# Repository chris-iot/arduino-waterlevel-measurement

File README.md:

# arduino-waterlevel-measurement
An Arduino based water level measurement that can e.g. be used to detect the fill level of your cistern

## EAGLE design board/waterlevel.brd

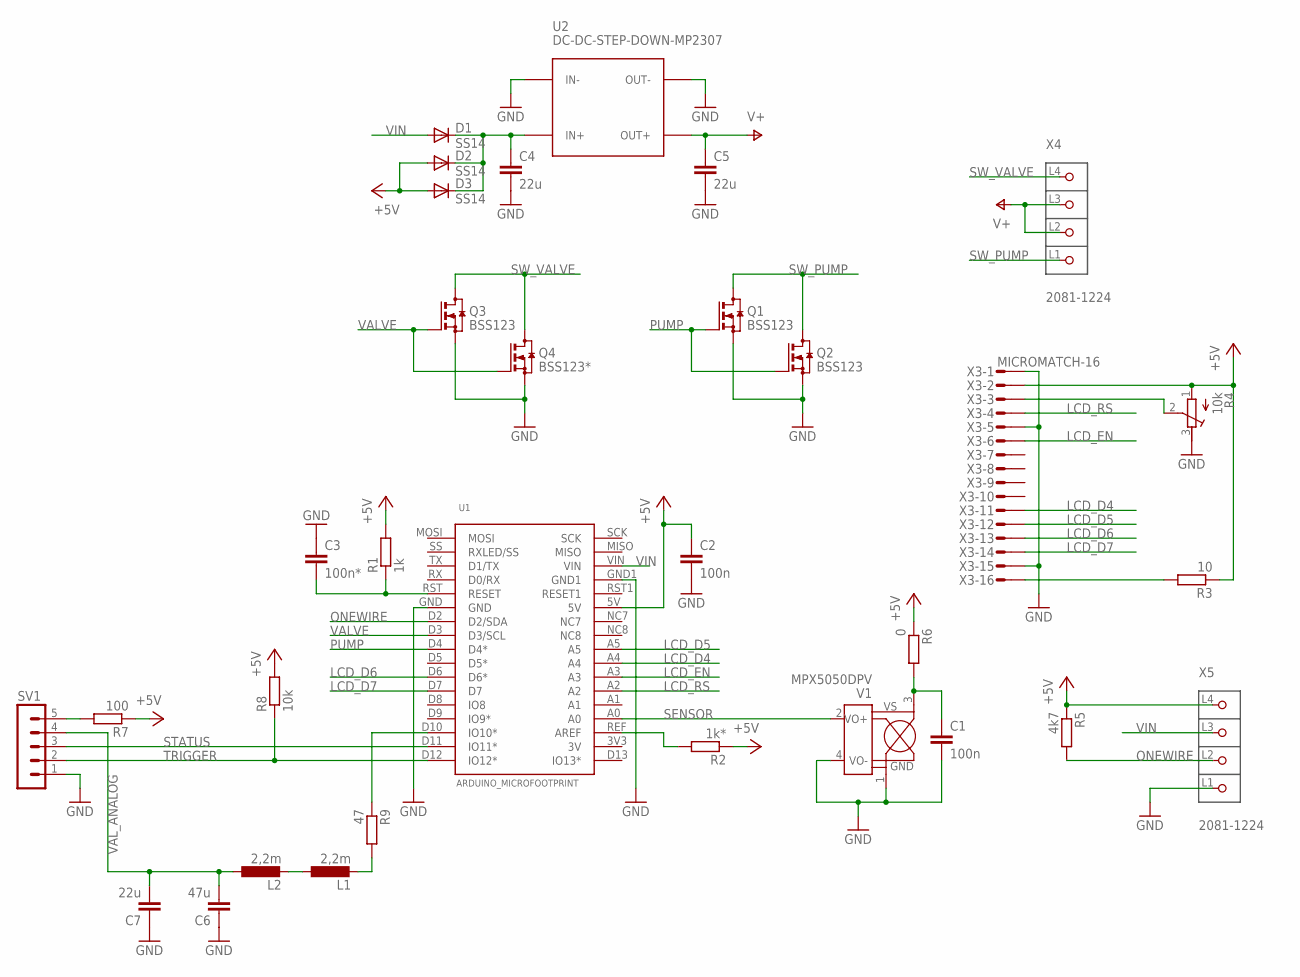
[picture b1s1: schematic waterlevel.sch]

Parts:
C1, C2: 100n; C0603
C3: 100n*; C0603
C4, C5: 22u; C1210K
C6: 47u; C1206K
C7: 22u; C1206K
D1, D2, D3: SS14; DO214AC
L1, L2: 2,2m; L1812
Q1, Q2, Q3: BSS123; SOT23
Q4: BSS123*; SOT23
R1: 1k; R0603
R2: 1k*; R0603
R3: 10; R0603
R4: 10k; RTRIM64Z
R5: 4k7; R0603
R6: 0; R0603
R7: 100; R0603
R8: 10k; R0603
R9: 47; R0603
SV1: MA05-1
U1: ARDUINO_MICROFOOTPRINT; ARDUINO-MICRO
U2: DC-DC-STEP-DOWN-MP2307
V1: MPX5050DPV; MPX2050DPV
X3: MICROMATCH-16
X4, X5: 2081-1224; P-2081-1224

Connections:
+5V: C2.1, D2.A, D3.A, R1.2, R2.1, R3.1, R4.1 (A), R5.1, R6.1, R7.1, R8.2, U1.5V, X3.2, X5.L4 (P4)
GND: C1.2, C2.2, C3.1, C4.2, C5.2, C6.1, C7.1, Q1.2 (S), Q2.2 (S), Q3.2 (S), Q4.2 (S), R4.3 (E), SV1.1, U1.GND, U1.GND1, U2.IN-, U2.OUT-, V1.1 (GND), V1.4 (VO-), X3.1, X3.5, X3.15, X5.L1 (P1)
LCD_D4: U1.A4, X3.11
LCD_D5: U1.A5, X3.12
LCD_D6: U1.D6 (D6*), X3.13
LCD_D7: U1.D7, X3.14
LCD_EN: U1.A3, X3.6
LCD_RS: U1.A2, X3.4
unnamed: C4.1, D1.C, D2.C, D3.C, U2.IN+
unnamed: C3.2, R1.1, U1.RST (RESET)
unnamed: R2.2, U1.REF (AREF)
unnamed: R4.2 (S), X3.3
unnamed: C1.1, R6.2, V1.3 (VS)
unnamed: R7.2, SV1.5
unnamed: R9.1, U1.D10 (IO10*)
unnamed: R3.2, X3.16
unnamed: L1.2, R9.2
unnamed: L1.1, L2.2
ONEWIRE: R5.2, U1.D2 (D2/SDA), X5.L2 (P2)
PUMP: Q1.1 (G), Q2.1 (G), U1.D4 (D4*)
SENSOR: U1.A0, V1.2 (VO+)
STATUS: SV1.3, U1.D11 (IO11*)
SW_PUMP: Q1.3 (D), Q2.3 (D), X4.L1 (P1)
SW_VALVE: Q3.3 (D), Q4.3 (D), X4.L4 (P4)
TRIGGER: R8.1, SV1.2, U1.D12 (IO12*)
V+: C5.1, U2.OUT+, X4.L2 (P2), X4.L3 (P3)
VALVE: Q3.1 (G), Q4.1 (G), U1.D3 (D3/SCL)
VAL_ANALOG: C6.2, C7.2, L2.1, SV1.4
VIN: D1.A, U1.VIN, X5.L3 (P3)

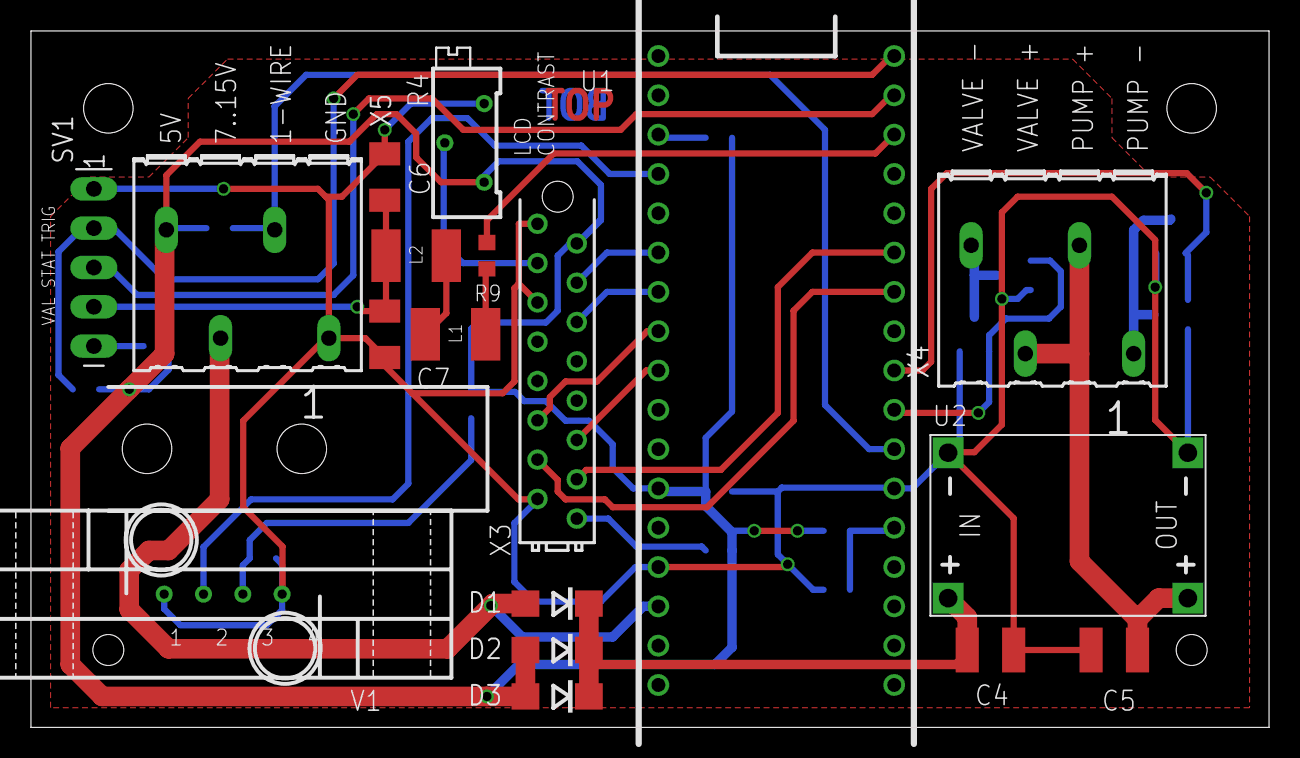
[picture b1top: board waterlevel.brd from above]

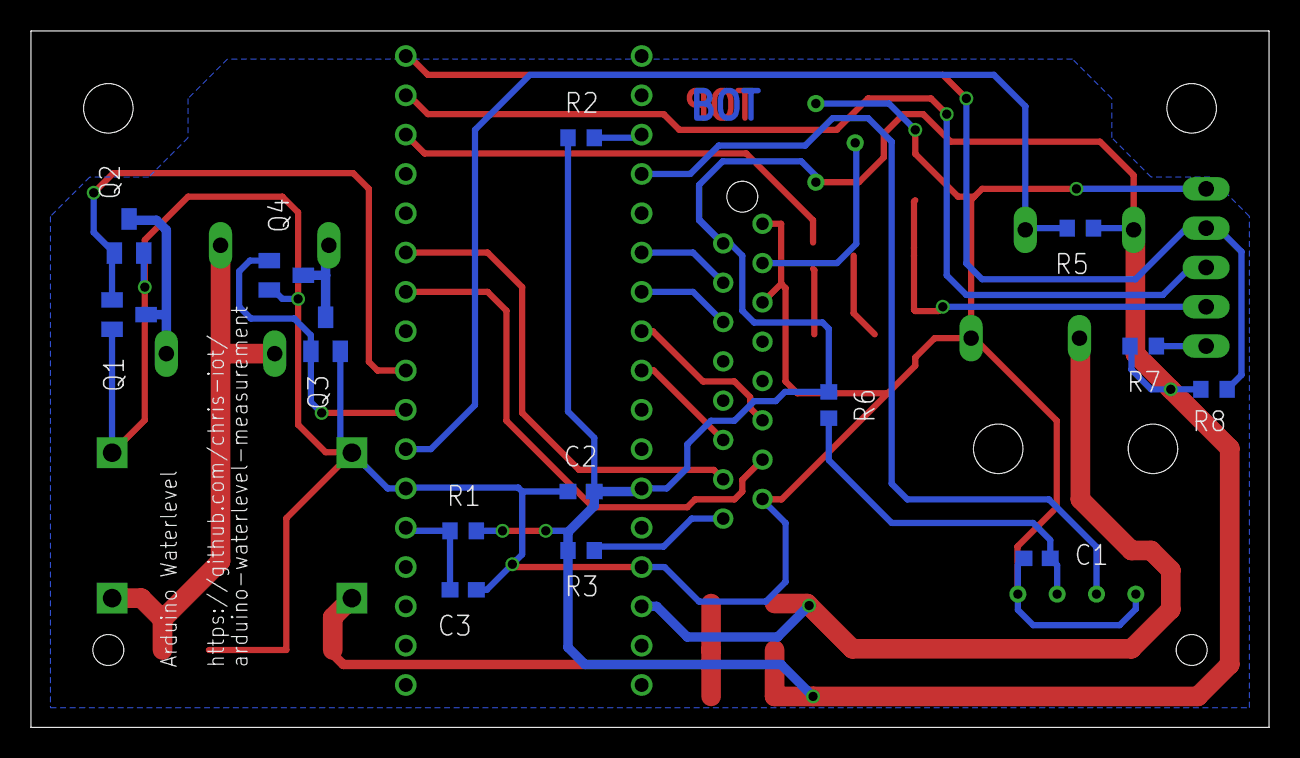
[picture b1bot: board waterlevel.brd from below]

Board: 2 copper layers, 80.0 x 45.0 mm, 32 parts (14 on the bottom side), 29 nets.

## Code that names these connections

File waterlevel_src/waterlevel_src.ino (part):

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const int valvepin = 3;
const int sensorpin = 0; //A0
const int onewireslavepin = 2; //this can either be D2 or D3 on the Arduino Nano as those are the only pins that can handle interrupts
const int lcd_rs = A2;
const int lcd_enable = A3;
const int lcd_d4 = A4;
const int lcd_d5 = A5;
const int lcd_d6 = 6; //D6
const int lcd_d7 = 7; //D7
const int valuepin = 10; //D10
const int statuspin = 11; //D11
const int triggerpin = 12; //D12
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  digitalWrite(pumppin,LOW);
}
void valve_close(){
  digitalWrite(valvepin,HIGH); //This assumes a "normally open" valve
}
void valve_open(){
  digitalWrite(valvepin,LOW);
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
void loop() {
  if(!digitalRead(triggerpin)){
    //trigger pin is low, check a few ms later again (debouncing)
    delay(200);
    if(!digitalRead(triggerpin)){
      //start the measurement
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
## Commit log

2018-11-11 Add initial source code (measurement functionality verified), sample measurements and mechanical parts (that are work in progress)
2018-11-11 Add timeout
2018-12-29 Add basic LCD support
2018-12-29 Add Displayholder, PCB guides and MPX sensor holder
2018-12-30 Export of all 3D print parts as stl files
2019-12-03 Add layout (incl. production files) and mechanics (incl. g-code for ABS prints)
2020-03-17 Add trigger and status support, minor fine tuning
2020-03-26 Bugfix for hour counter

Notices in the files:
parts and their libraries:
diy-modules: Released under the Creative Commons Attribution 4.0 International License: http://creativecommons.org/licenses/by/4.0
